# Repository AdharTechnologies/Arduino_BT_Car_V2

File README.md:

# Arduino_BT_Car_V2

#Description
Arduino Nano based Bluetooth Car. This is version 2. In this version we have used DRV8833 motor driver and the project is done on a PCB

kindly read this blog for full understanding: https://docs.google.com/document/d/e/2PACX-1vSI_xwrb_gmhYPVUlGB_xqGtsml429y3KM-hlfEuB1qynFKzpxm-LoXADPWcJAX5hsCF3Su3da1zLT_/pub 

# Embedded CTG

Facebook:https://www.facebook.com/profile.php?id=61558436573900

Youtube: https://www.youtube.com/@EmbeddedCTG

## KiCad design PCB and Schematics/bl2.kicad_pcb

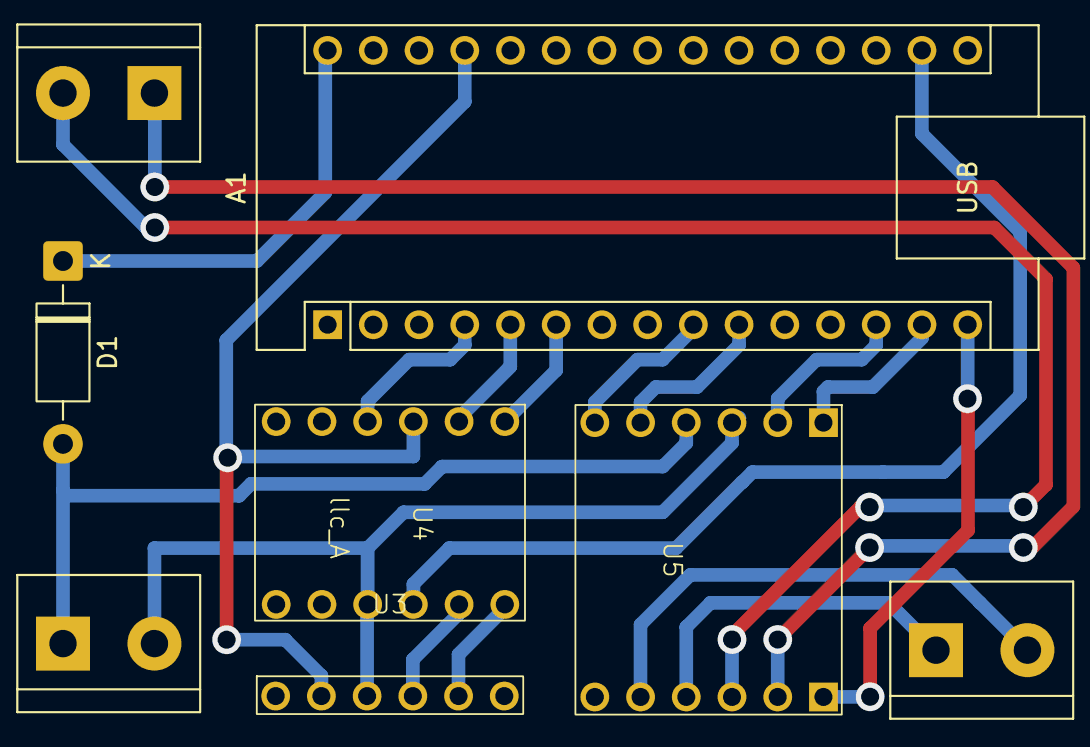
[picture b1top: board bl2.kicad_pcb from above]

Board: 2 copper layers, 5 parts (0 on the bottom side), 14 nets.

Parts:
A1: Arduino_Nano_v3.x; Arduino_Nano
D1: 1N4007; D_DO-41_SOD81_P10.16mm_Horizontal
U3: HC05_A
U4: llc_A
U5: DRV8833_A_2

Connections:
+3.3V: A1.17 (3V3), U4.3 (LV)
+5V: A1.27 (+5V), U3.2 (VCC), U4.9 (HV)
GND: A1.4 (GND), A1.29 (GND), U3.3 (GND), U4.4 (GND), U4.10 (GND), U5.9 (GND)
ML1: A1.14 (D11), U5.7 (IN4)
ML2: A1.13 (D10), U5.8 (IN3)
MR1: A1.9 (D6), U5.12 (IN1)
MR2: A1.10 (D7), U5.11 (IN2)
NRX: A1.6 (D3), U4.7 (HV1)
NTX: A1.5 (D2), U4.8 (HV2)
unnamed: A1.30 (VIN), D1.1 (K)
SLEEP: A1.15 (D12), U5.1 (EEP)
VBUS: D1.2 (A), U5.10 (VCC)
llcRX: U3.5 (RX), U4.1 (LV1)
llcTX: U3.4 (TX), U4.2 (LV2)

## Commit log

2025-07-27 README.md
